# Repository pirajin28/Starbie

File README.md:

# Starbie — Half Life Week 1 KiCad draft

This project is based on SharKingStudios/Starbie's Week 1 guide and the supplied Week 1 Care Package.

## Files
- `Starbie.kicad_pro` — KiCad project
- `Starbie.kicad_sch` — editable schematic draft
- `Starbie.kicad_pcb` — editable PCB placement/net draft
- `Imported Parts.pretty/` — supplied OLED, MPU6050 and XIAO footprints
- `StarbieParts.pretty/` — helper footprints for the DHT11 header and buttons
- `Seeed_Studio_XIAO_Series.kicad_sym` — supplied Seeed symbol library
- `3D Models/` — supplied STEP models

## Pin/net map
| Function | XIAO ESP32-C3 label | GPIO | PCB net |
|---|---|---:|---|
| OLED SDA + MPU6050 SDA | D4 | GPIO6 | `I2C_SDA` |
| OLED SCL + MPU6050 SCL | D5 | GPIO7 | `I2C_SCL` |
| DHT11 data | D1 | GPIO3 | `DHT_DATA` |
| Button 1 | D2 | GPIO4 | `BUTTON_1` |
| Button 2 | D3 | GPIO5 | `BUTTON_2` |
| Power | 3V3 | — | `3V3` |
| Ground | GND | — | `GND` |

The OLED footprint uses the care-package pad order: 1=GND, 2=VDD, 3=SCL, 4=SDA.
The MPU6050 module footprint is mapped as 1=VCC, 2=GND, 3=SCL, 4=SDA; pads 5–8 are left unconnected.
The DHT11 header is mapped 1=3V3, 2=DATA, 3=NC, 4=GND.
Buttons are modeled as generic 2-pad through-hole switches; verify that this matches the actual switch style you plan to use.

## IMPORTANT: current status
This is an **editable first-pass draft**, not a fabrication-ready board. The PCB footprints are placed and nets are assigned, but the copper tracks have **not** been routed, no ground pour has been added, and DRC has not been run in KiCad. Do not order a PCB from this draft yet.

## Next steps in KiCad
1. Open `Starbie.kicad_pro`.
2. Open the schematic and check that the labels are attached to the intended pins.
3. Open PCB Editor and run **Update PCB from Schematic** if needed.
4. Finish arranging footprints, route every airwire on F.Cu/B.Cu, add a GND zone if desired, and refill zones.
5. Run **Inspect → Design Rules Checker** and resolve all errors/unconnected nets.
6. Save, then export Gerbers and drill files only after the board is fully checked.

Reference: https://github.com/SharKingStudios/Starbie/blob/main/Week%201%20Guide.md

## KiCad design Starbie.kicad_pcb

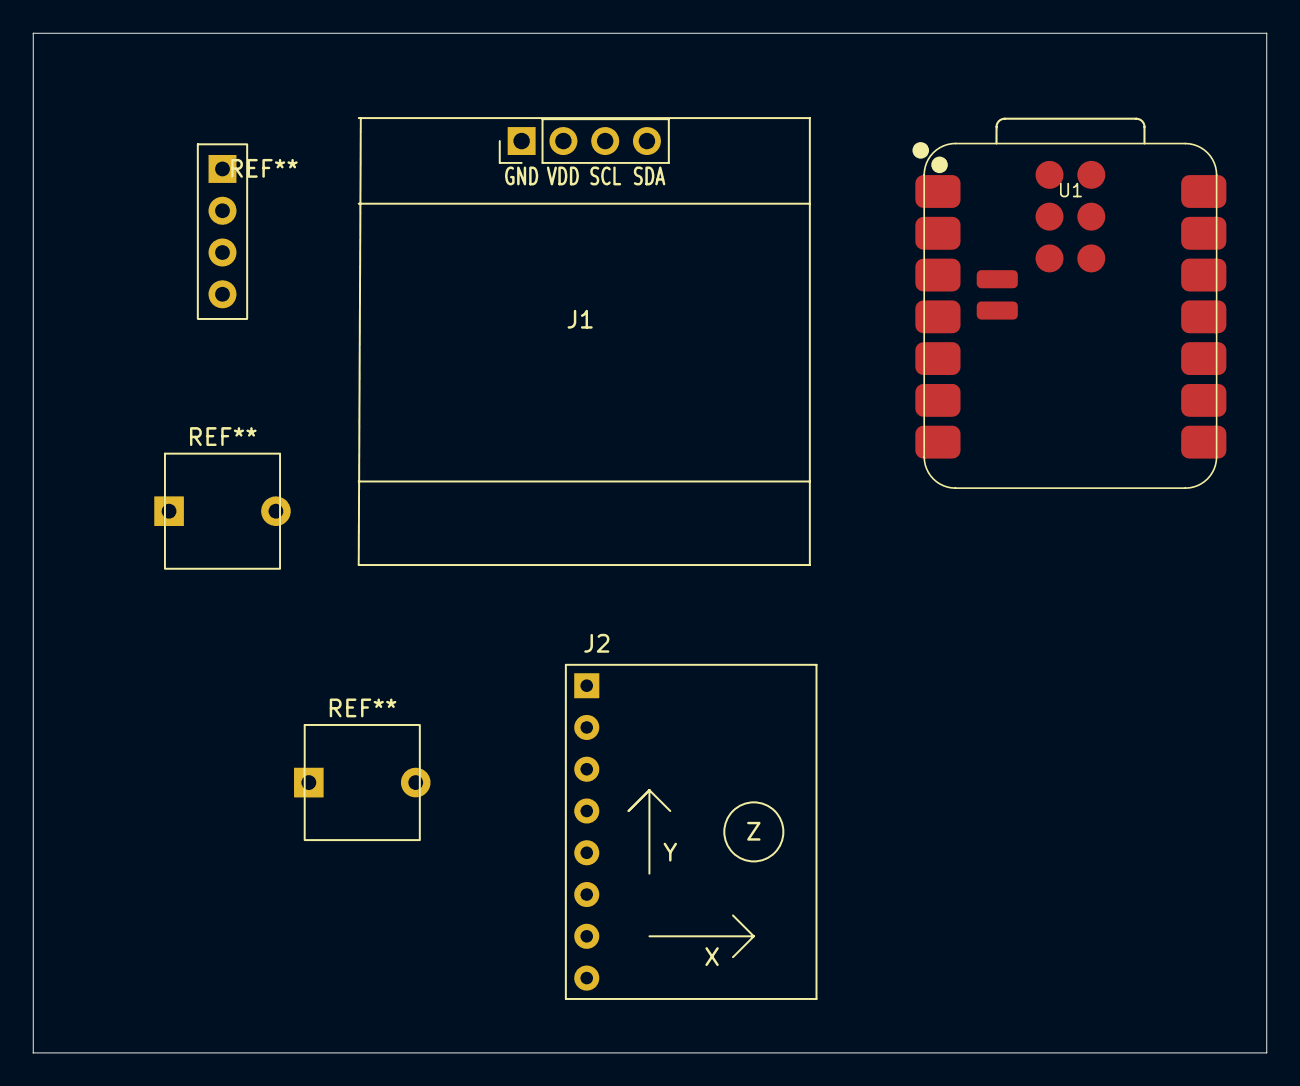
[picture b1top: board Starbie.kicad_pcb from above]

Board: 2 copper layers, 75.0 x 62.0 mm, 3 parts (0 on the bottom side), 4 nets, no tracks yet.

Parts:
J1: OLED_128x64_I2C; Display_128x64_096_I2C
J2: MPU6050_Module
U1: XIAO-ESP32-C3-SMD

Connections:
3V3: J1.2, J2.1, U1.12
GND: J1.1, J2.2, U1.13
I2C_SCL: J1.3, J2.3, U1.6
I2C_SDA: J1.4, J2.4, U1.5
